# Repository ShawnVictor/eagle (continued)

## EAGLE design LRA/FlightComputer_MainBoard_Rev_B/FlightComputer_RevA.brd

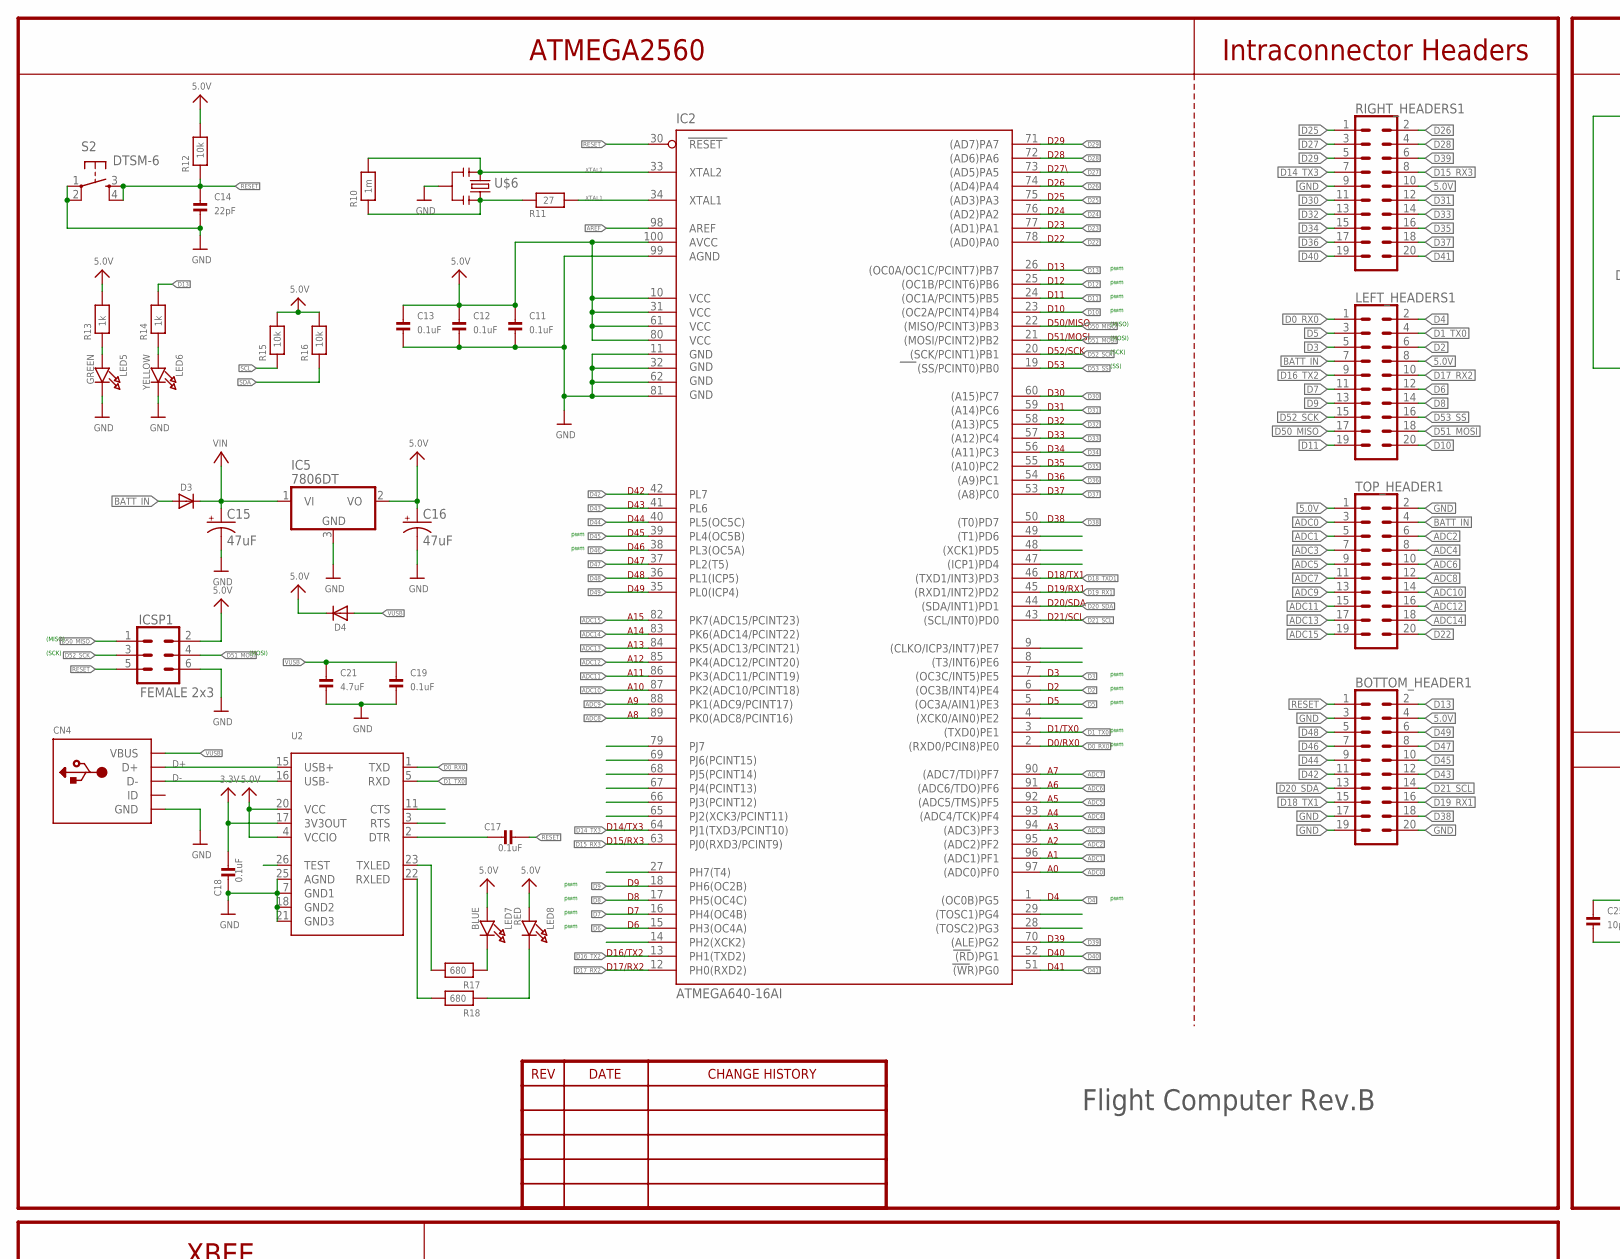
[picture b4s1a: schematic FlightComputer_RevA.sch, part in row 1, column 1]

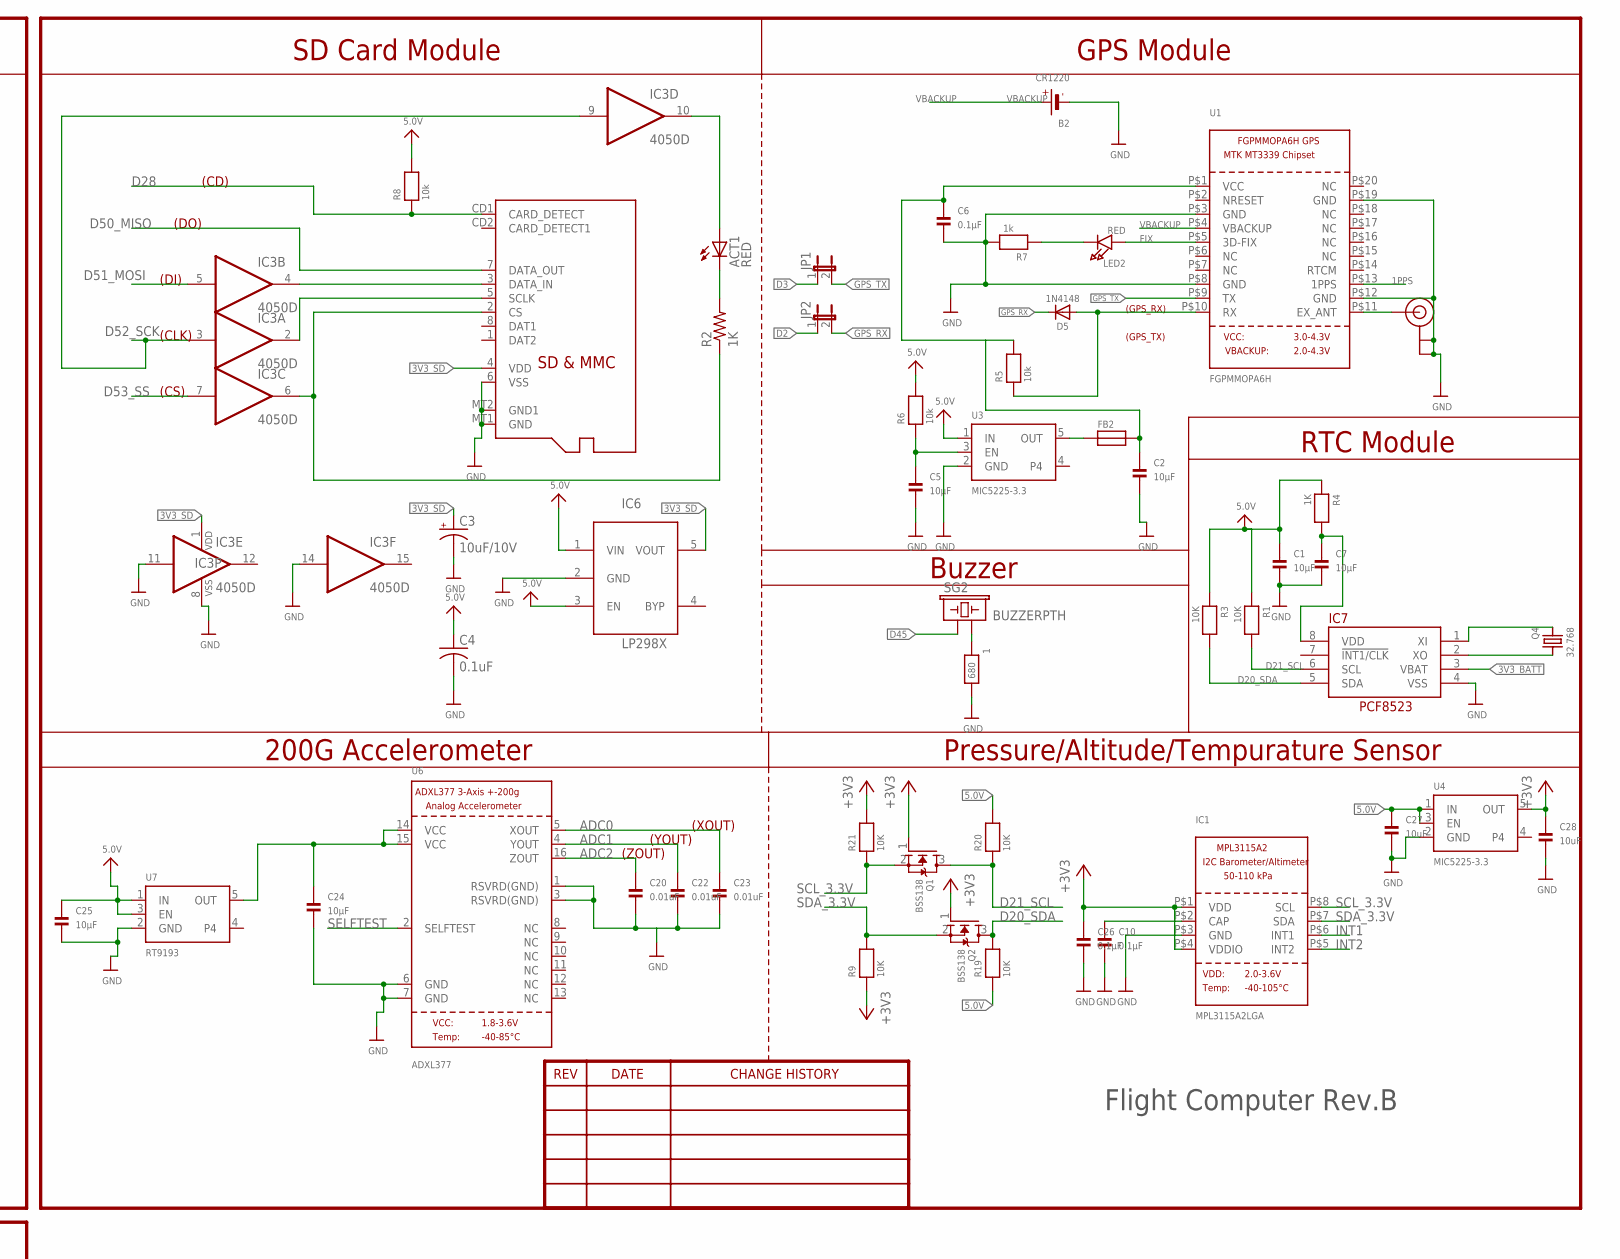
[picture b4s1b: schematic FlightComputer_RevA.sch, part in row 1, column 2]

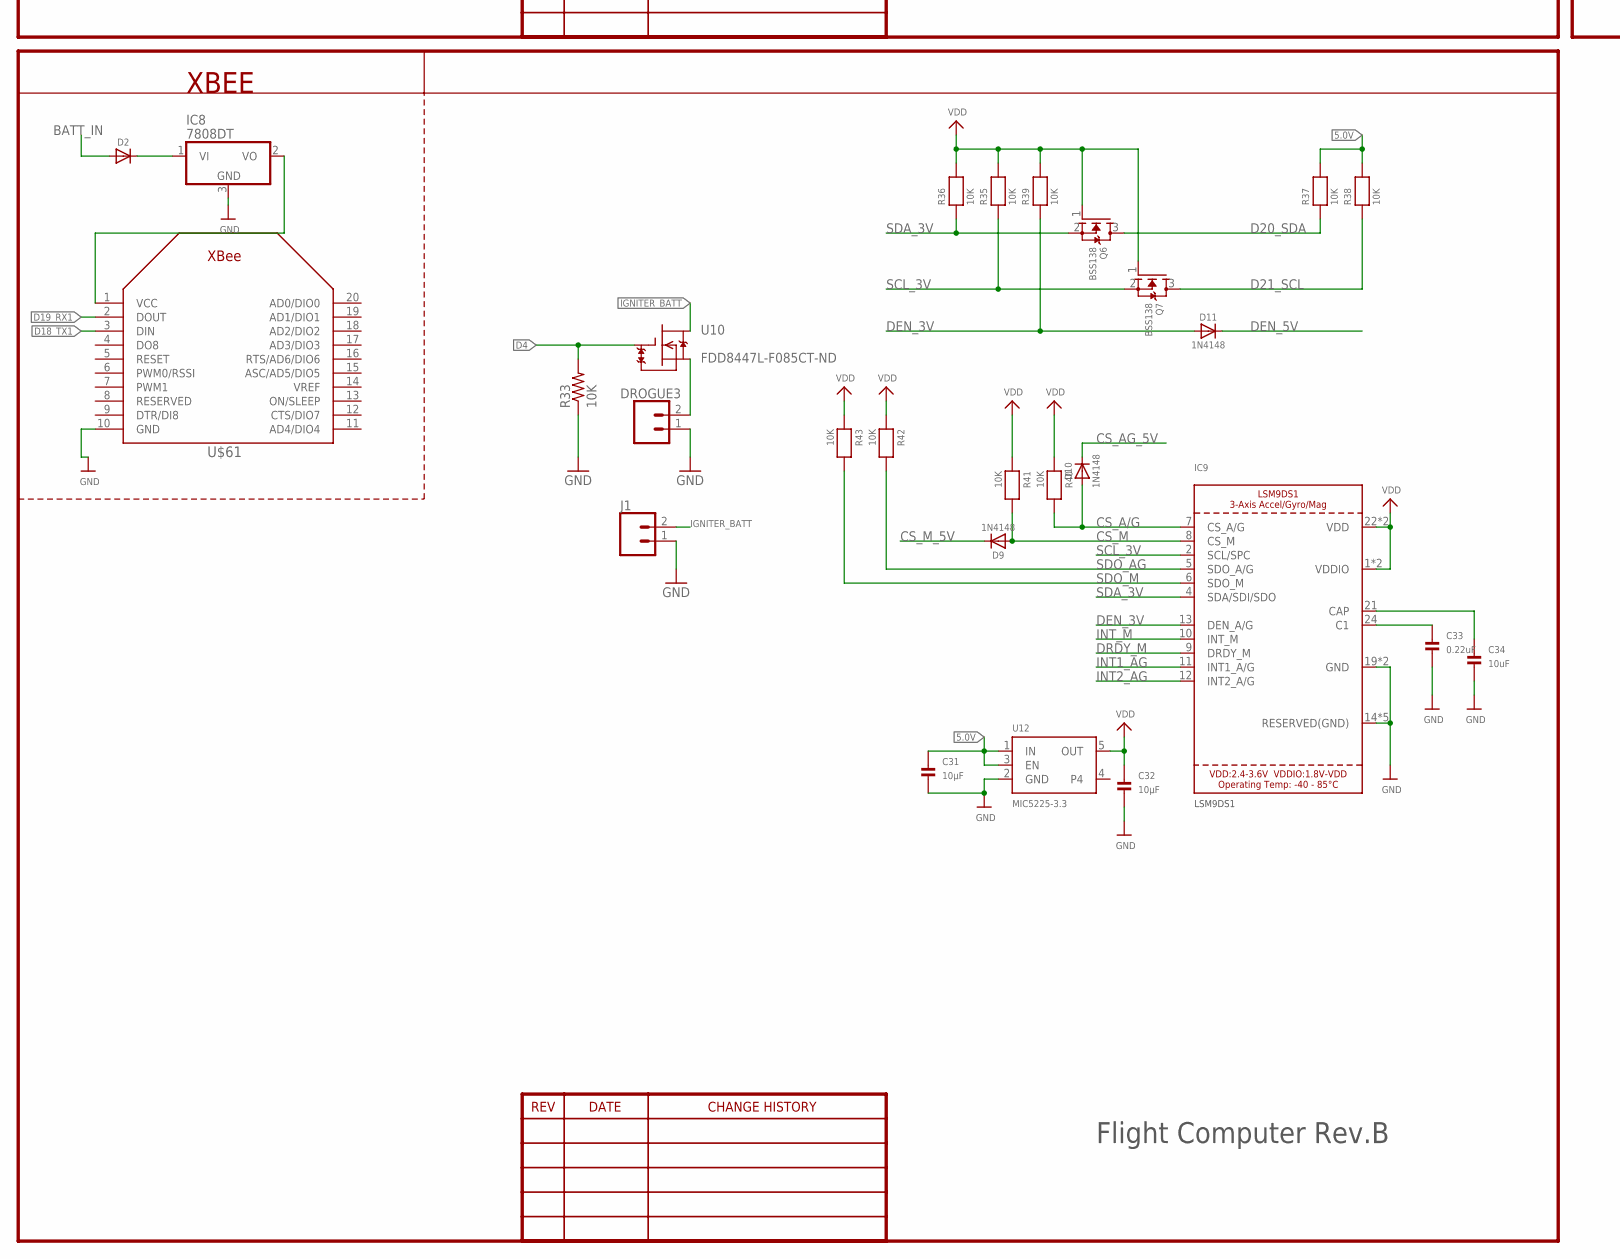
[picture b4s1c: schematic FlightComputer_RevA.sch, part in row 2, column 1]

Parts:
1: 680; 0603
ACT1: RED; CHIP-LED0805
B2: CR1220
BOTTOM_HEADER1: CONN_10X2; 2X10
C1, C2, C5, C7, C24, C25, C31, C32: 10µF; 0603
C3: 10uF/10V; A/3216-18R
C4: 0.1uF; C0805K
C6, C10, C26: 0.1µF; 0603
C11, C12, C13, C17, C18, C19: 0.1uF; 0805
C14: 22pF; 0805
C15, C16: 47uF; PANASONIC_D
C20, C22, C23: 0.01uF; 0603
C21: 4.7uF; 0805
C27, C28, C34: 10uF; 0603
C33: 0.22uF; 0603
CN4: USBMINIB; USB-MINIB
D2, D3, D4: DIODESOD-123; SOD-123
D5, D9, D10, D11: 1N4148; SOD-323
DROGUE3: CONN_023.5MM; SCREWTERMINAL-3.5MM-2
FB2: FERRITE; 0603
IC1: MPL3115A2LGA; LGA8
IC2: ATMEGA640-16AI; TQFP100
IC3: 4050D; SO16
IC5: 7806DT; TO252
IC6: LP298XS; SOT23-5L
IC7: RTC_PCF8523T; SOIC8_150MIL
IC8: 7808DT; TO252
IC9: LSM9DS1; LGA24_3.5X3.1MM
ICSP1: FEMALE 2x3; 2X3
J1: CONN_02; 1X02
JP1, JP2: JUMPER-2SMD-NO-NS; SJ_2S-NO-NS
LED2, LED8: RED; CHIPLED_0805
LED5: GREEN; CHIPLED_0805
LED6: YELLOW; CHIPLED_0805
LED7: BLUE; CHIPLED_0805
LEFT_HEADERS1: CONN_10X2; 2X10
Q1, Q2, Q6, Q7: BSS138; SOT23-WIDE
Q4: 32.768; CRYSTAL_8X3.8
R1, R3, R9, R19, R20, R21, R35, R36, R37, R38, R39, R40, R41, R42, R43: 10K; 0603
R2: 1K; R0805
R4: 1K; 0603
R5, R6, R8: 10k; 0603
R7: 1k; 0603
R10: 1m; 0805
R11: 27; 0805
R12, R15, R16: 10k; 0805
R13, R14: 1k; 0805
R17, R18: 680; 0805
R33: 10K; R0805
RIGHT_HEADERS1: CONN_10X2; 2X10
S2: DTSM-6
SG2: BUZZERPTH; BUZZER-12MM
TOP_HEADER1: CONN_10X2; 2X10
U1: FGPMMOPA6H
U2: FT232RLSSOP28; SSOP28DB
U3, U4, U12: MIC5225-3.3; SOT23-5
U6: ADXL377; LFCSP16_LQ
U7: RT9193; SOT23-5
U10: FDD8447L-F085CT-ND; TO252
U$1: U.FL
U$6: RESONATORSMD; RESONATOR-SMD
U$61: XBEE
X2: MICROSD

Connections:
1PPS: U1.P$13 (1PPS)
3.3V: C18.2, U2.17 (3V3OUT)
3V3_BATT: IC7.3 (VBAT)
3V3_SD: C3.+, IC3.1 (VDD), IC6.5 (VOUT), X2.4 (VDD)
5.0V: BOTTOM_HEADER1.4, C1.1, C4.1, C11.1, C12.1, C13.1, C16.+, C25.1, C27.1, C31.1, D4.C, IC2.10 (VCC), IC2.31 (VCC1), IC2.61 (VCC2), IC2.80 (VCC3), IC2.100 (AVCC), IC5.2 (VO), IC6.1 (VIN), IC6.3 (EN), ICSP1.2, LED7.A, LED8.A, LEFT_HEADERS1.8, R1.1, R3.1, R4.1, R6.2, R8.2, R12.2, R13.2, R15.2, R16.2, R19.1, R20.2, R37.2, R38.2, RIGHT_HEADERS1.10, TOP_HEADER1.1, U2.4 (VCCIO), U2.20 (VCC), U3.1 (IN), U4.1 (IN), U4.3 (EN), U7.1 (IN), U7.3 (EN), U12.1 (IN), U12.3 (EN)
+3V3: C26.1, C28.1, IC1.P$1 (VDD), IC1.P$4 (VDDIO), Q1.1 (G), Q2.1 (G), R9.1, R21.2, U4.5 (OUT)
ADC0: C23.1, IC2.97 ((ADC0)PF0), TOP_HEADER1.3, U6.5 (XOUT)
ADC1: C22.1, IC2.96 ((ADC1)PF1), TOP_HEADER1.5, U6.4 (YOUT)
ADC2: C20.1, IC2.95 ((ADC2)PF2), TOP_HEADER1.6, U6.16 (ZOUT)
ADC3: IC2.94 ((ADC3)PF3), TOP_HEADER1.7
ADC4: IC2.93 ((ADC4/TCK)PF4), TOP_HEADER1.8
ADC5: IC2.92 ((ADC5/TMS)PF5), TOP_HEADER1.9
ADC6: IC2.91 ((ADC6/TDO)PF6), TOP_HEADER1.10
ADC7: IC2.90 ((ADC7/TDI)PF7), TOP_HEADER1.11
ADC8: IC2.89 (PK0(ADC8/PCINT16)), TOP_HEADER1.12
ADC9: IC2.88 (PK1(ADC9/PCINT17)), TOP_HEADER1.13
ADC10: IC2.87 (PK2(ADC10/PCINT18)), TOP_HEADER1.14
ADC11: IC2.86 (PK3(ADC11/PCINT19)), TOP_HEADER1.15
ADC12: IC2.85 (PK4(ADC12/PCINT20)), TOP_HEADER1.16
ADC13: IC2.84 (PK5(ADC13/PCINT21)), TOP_HEADER1.17
ADC14: IC2.83 (PK6(ADC14/PCINT22)), TOP_HEADER1.18
ADC15: IC2.82 (PK7(ADC15/PCINT23)), TOP_HEADER1.19
AREF: IC2.98 (AREF)
BATT_IN: D2.A, D3.A, LEFT_HEADERS1.7, TOP_HEADER1.4
C1: C33.1, IC9.24 (C1)
CAP1: C10.1, IC1.P$2 (CAP)
CAP3: C34.1, IC9.21 (CAP)
CS_A/G: D10.A, IC9.7 (CS_A/G), R40.2
CS_AG_5V: D10.C
CS_M: D9.A, IC9.8 (CS_M), R41.2
CS_M_5V: D9.C
D0_RX0: IC2.2 ((RXD0/PCIN8)PE0), LEFT_HEADERS1.1, U2.1 (TXD)
D1_TX0: IC2.3 ((TXD0)PE1), LEFT_HEADERS1.4, U2.5 (RXD)
D2: IC2.6 ((OC3B/INT4)PE4), JP2.1, LEFT_HEADERS1.6
D3: IC2.7 ((OC3C/INT5)PE5), JP1.1, LEFT_HEADERS1.5
D4: IC2.1 ((OC0B)PG5), LEFT_HEADERS1.2, R33.2, U10.G
D5: IC2.5 ((OC3A/AIN1)PE3), LEFT_HEADERS1.3
D6: IC2.15 (PH3(OC4A)), LEFT_HEADERS1.12
D7: IC2.16 (PH4(OC4B)), LEFT_HEADERS1.11
D8: IC2.17 (PH5(OC4C)), LEFT_HEADERS1.14
D9: IC2.18 (PH6(OC2B)), LEFT_HEADERS1.13
D10: IC2.23 ((OC2A/PCINT4)PB4), LEFT_HEADERS1.20
D11: IC2.24 ((OC1A/PCINT5)PB5), LEFT_HEADERS1.19
D12: IC2.25 ((OC1B/PCINT6)PB6)
D13: BOTTOM_HEADER1.2, IC2.26 ((OC0A/OC1C/PCINT7)PB7), R14.2
D14_TX3: IC2.64 (PJ1(TXD3/PCINT10)), RIGHT_HEADERS1.7
D15_RX3: IC2.63 (PJ0(RXD3/PCINT9)), RIGHT_HEADERS1.8
D16_TX2: IC2.13 (PH1(TXD2)), LEFT_HEADERS1.9
D17_RX2: IC2.12 (PH0(RXD2)), LEFT_HEADERS1.10
D18_TX1: BOTTOM_HEADER1.15, U$61.3 (DIN)
D18_TXD1: IC2.46 ((TXD1/INT3)PD3)
D19_RX1: BOTTOM_HEADER1.16, IC2.45 ((RXD1/INT2)PD2), U$61.2 (DOUT)
D20_SDA: BOTTOM_HEADER1.13, IC2.44 ((SDA/INT1)PD1), IC7.5 (SDA), Q2.3 (D), Q6.3 (D), R3.2, R19.2, R37.1
D21_SCL: BOTTOM_HEADER1.14, IC2.43 ((SCL/INT0)PD0), IC7.6 (SCL), Q1.3 (D), Q7.3 (D), R1.2, R20.1, R38.1
D22: IC2.78 ((AD0)PA0), TOP_HEADER1.20
D23: IC2.77 ((AD1)PA1)
D24: IC2.76 ((AD2)PA2)
D25: IC2.75 ((AD3)PA3), RIGHT_HEADERS1.1
D26: IC2.74 ((AD4)PA4), RIGHT_HEADERS1.2
D27: IC2.73 ((AD5)PA5), RIGHT_HEADERS1.3
D28: IC2.72 ((AD6)PA6), R8.1, RIGHT_HEADERS1.4, X2.CD1 (CARD_DETECT)
D29: IC2.71 ((AD7)PA7), RIGHT_HEADERS1.5
D30: IC2.60 ((A15)PC7), RIGHT_HEADERS1.11
D31: IC2.59 ((A14)PC6), RIGHT_HEADERS1.12
D32: IC2.58 ((A13)PC5), RIGHT_HEADERS1.13
D33: IC2.57 ((A12)PC4), RIGHT_HEADERS1.14
D34: IC2.56 ((A11)PC3), RIGHT_HEADERS1.15
D35: IC2.55 ((A10)PC2), RIGHT_HEADERS1.16
D36: IC2.54 ((A9)PC1), RIGHT_HEADERS1.17
D37: IC2.53 ((A8)PC0), RIGHT_HEADERS1.18
D38: BOTTOM_HEADER1.18, IC2.50 ((T0)PD7)
D39: IC2.70 ((ALE)PG2), RIGHT_HEADERS1.6
D40: IC2.52 ((RD)PG1), RIGHT_HEADERS1.19
D41: IC2.51 ((WR)PG0), RIGHT_HEADERS1.20
D42: BOTTOM_HEADER1.11, IC2.42 (PL7)
D43: BOTTOM_HEADER1.12, IC2.41 (PL6)
D44: BOTTOM_HEADER1.9, IC2.40 (PL5(OC5C))
D45: BOTTOM_HEADER1.10, IC2.39 (PL4(OC5B)), SG2.+ (1)
D46: BOTTOM_HEADER1.7, IC2.38 (PL3(OC5A))
D47: BOTTOM_HEADER1.8, IC2.37 (PL2(T5))
D48: BOTTOM_HEADER1.5, IC2.36 (PL1(ICP5))
D49: BOTTOM_HEADER1.6, IC2.35 (PL0(ICP4))
D50_MISO: IC2.22 ((MISO/PCINT3)PB3), ICSP1.1, LEFT_HEADERS1.17, X2.7 (DATA_OUT)
D51_MOSI: IC2.21 ((MOSI/PCINT2)PB2), IC3.5 (I), ICSP1.4, LEFT_HEADERS1.18
D52_SCK: IC2.20 ((SCK/PCINT1)PB1), IC3.3 (I), IC3.9 (I), ICSP1.3, LEFT_HEADERS1.15
D53_SS: IC2.19 ((SS/PCINT0)PB0), IC3.7 (I), LEFT_HEADERS1.16
D+: CN4.D+, U2.15 (USB+)
D-: CN4.D-, U2.16 (USB-)
DEN_3V: D11.A, IC9.13 (DEN_A/G), R39.1
DEN_5V: D11.C
DRDY_M: IC9.9 (DRDY_M)
FIX: LED2.A, U1.P$5 (3D-FIX)
GND: 1.2, B2.-, BOTTOM_HEADER1.3, BOTTOM_HEADER1.17, BOTTOM_HEADER1.19, BOTTOM_HEADER1.20, C1.2, C2.2, C3.-, C4.2, C5.2, C6.2, C7.2, C10.2, C11.2, C12.2, C13.2, C14.2, C15.-, C16.-, C18.1, C19.1, C20.2, C21.1, C22.2, C23.2, C24.2, C25.2, C26.2, C27.2, C28.2, C31.2, C32.2, C33.2, C34.2, CN4.GND, DROGUE3.1, IC1.P$3 (GND), IC2.11 (GND), IC2.32 (GND1), IC2.62 (GND2), IC2.81 (GND3), IC2.99 (AGND), IC3.8 (VSS), IC3.11 (I), IC3.14 (I), IC5.3 (GND), IC6.2 (GND), IC7.4 (VSS), IC8.3 (GND), IC9.14 (RESERVED(GND)), IC9.15 (RESERVED(GND)), IC9.16 (RESERVED(GND)), IC9.17 (RESERVED(GND)), IC9.18 (RESERVED(GND)), IC9.19 (GND), IC9.20 (GND), ICSP1.6, J1.1, LED5.C, LED6.C, R7.2, R33.1, RIGHT_HEADERS1.9, S2.1, S2.2, TOP_HEADER1.2, U1.P$3 (GND), U1.P$8 (GND), U1.P$12 (GND), U1.P$19 (GND), U2.7 (GND1), U2.18 (GND2), U2.21 (GND3), U2.25 (AGND), U3.2 (GND), U4.2 (GND), U6.1 (RSVRD(GND)), U6.3 (RSVRD(GND)), U6.6 (GND), U6.7 (GND), U7.2 (GND), U12.2 (GND), U$1.P$1 (GND), U$1.P$2 (GND), U$6.2, U$61.10 (GND), X2.6 (VSS), X2.MT1 (GND), X2.MT2 (GND1)
GPS_RX: D5.C, JP2.2
GPS_TX: JP1.2, U1.P$9 (TX)
IGNITER_BATT: J1.2, U10.D
INT1: IC1.P$6 (INT1)
INT1_AG: IC9.11 (INT1_A/G)
INT2: IC1.P$5 (INT2)
INT2_AG: IC9.12 (INT2_A/G)
INT_M: IC9.10 (INT_M)
unnamed: IC7.1 (XI), Q4.P$1 (1)
unnamed: IC7.2 (XO), Q4.P$4 (2)
unnamed: ACT1.A, IC3.10 (O)
unnamed: IC3.2 (O), X2.5 (SCLK)
unnamed: IC3.6 (O), R2.1, X2.2 (CS)
unnamed: ACT1.C, R2.2
unnamed: IC3.4 (O), X2.3 (DATA_IN)
unnamed: C7.1, IC7.8 (VDD), R4.2
unnamed: U1.P$11 (EX_ANT), U$1.P$3 (SIGNAL)
unnamed: D5.A, R5.1, U1.P$10 (RX)
unnamed: C2.1, C6.1, FB2.2, R5.2, U1.P$1 (VCC)
unnamed: R10.1, R11.2, U$6.3
unnamed: C5.1, R6.1, U3.3 (EN)
unnamed: LED2.C, R7.1
unnamed: D2.C, IC8.1 (VI)
unnamed: 1.1, SG2.- (2)
unnamed: C24.1, IC2.14 (PH2(XCK2)), U6.14 (VCC), U6.15 (VCC), U7.5 (OUT)
unnamed: LED5.A, R13.1
unnamed: LED6.A, R14.1
unnamed: LED8.C, R18.1
unnamed: LED7.C, R17.1
unnamed: C17.1, U2.2 (DTR)
unnamed: R18.2, U2.22 (RXLED)
unnamed: R17.2, U2.23 (TXLED)
OUT: FB2.1, U3.5 (OUT)
RESET: BOTTOM_HEADER1.1, C14.1, C17.2, IC2.30 (RESET), ICSP1.5, R12.1, S2.3, S2.4
SCL: R15.1
SCL_3.3V: IC1.P$8 (SCL), Q1.2 (S), R21.1
SCL_3V: IC9.2 (SCL/SPC), Q7.2 (S), R35.1
SDA: R16.1
SDA_3.3V: IC1.P$7 (SDA), Q2.2 (S), R9.2
SDA_3V: IC9.4 (SDA/SDI/SDO), Q6.2 (S), R36.1
SDO_AG: IC9.5 (SDO_A/G), R42.2
SDO_M: IC9.6 (SDO_M), R43.2
SELFTEST: U6.2 (SELFTEST)
SOURCE2: DROGUE3.2, U10.S
VBACKUP: B2.+$1 (+), B2.+$2 (+), U1.P$4 (VBACKUP)
VCC: IC8.2 (VO), U$61.1 (VCC)
VDD: C32.1, IC9.1 (VDDIO), IC9.3 (VDDIO), IC9.22 (VDD), IC9.23 (VDD), Q6.1 (G), Q7.1 (G), R35.2, R36.2, R39.2, R40.1, R41.1, R42.1, R43.1, U12.5 (OUT)
VIN: C15.+, D3.C, IC5.1 (VI)
VUSB: C19.2, C21.2, CN4.VBUS, D4.A
XTAL1: IC2.34 (XTAL1), R11.1
XTAL2: IC2.33 (XTAL2), R10.2, U$6.1

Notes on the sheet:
Intraconnector Headers
pwm
(SS)
(SCK)
(MOSI)
(MISO)
D42
D43
D44
D45
D46
D47
D48
D49
A15
A14
A13
A12
A11
A10
D14/TX3
D15/RX3
D16/TX2
D17/RX2
D29
D28
D27\
D26
D25
D24
D23
D22
D13
D12
D11
D10
D50/MISO
D51/MOSI
D52/SCK
D53

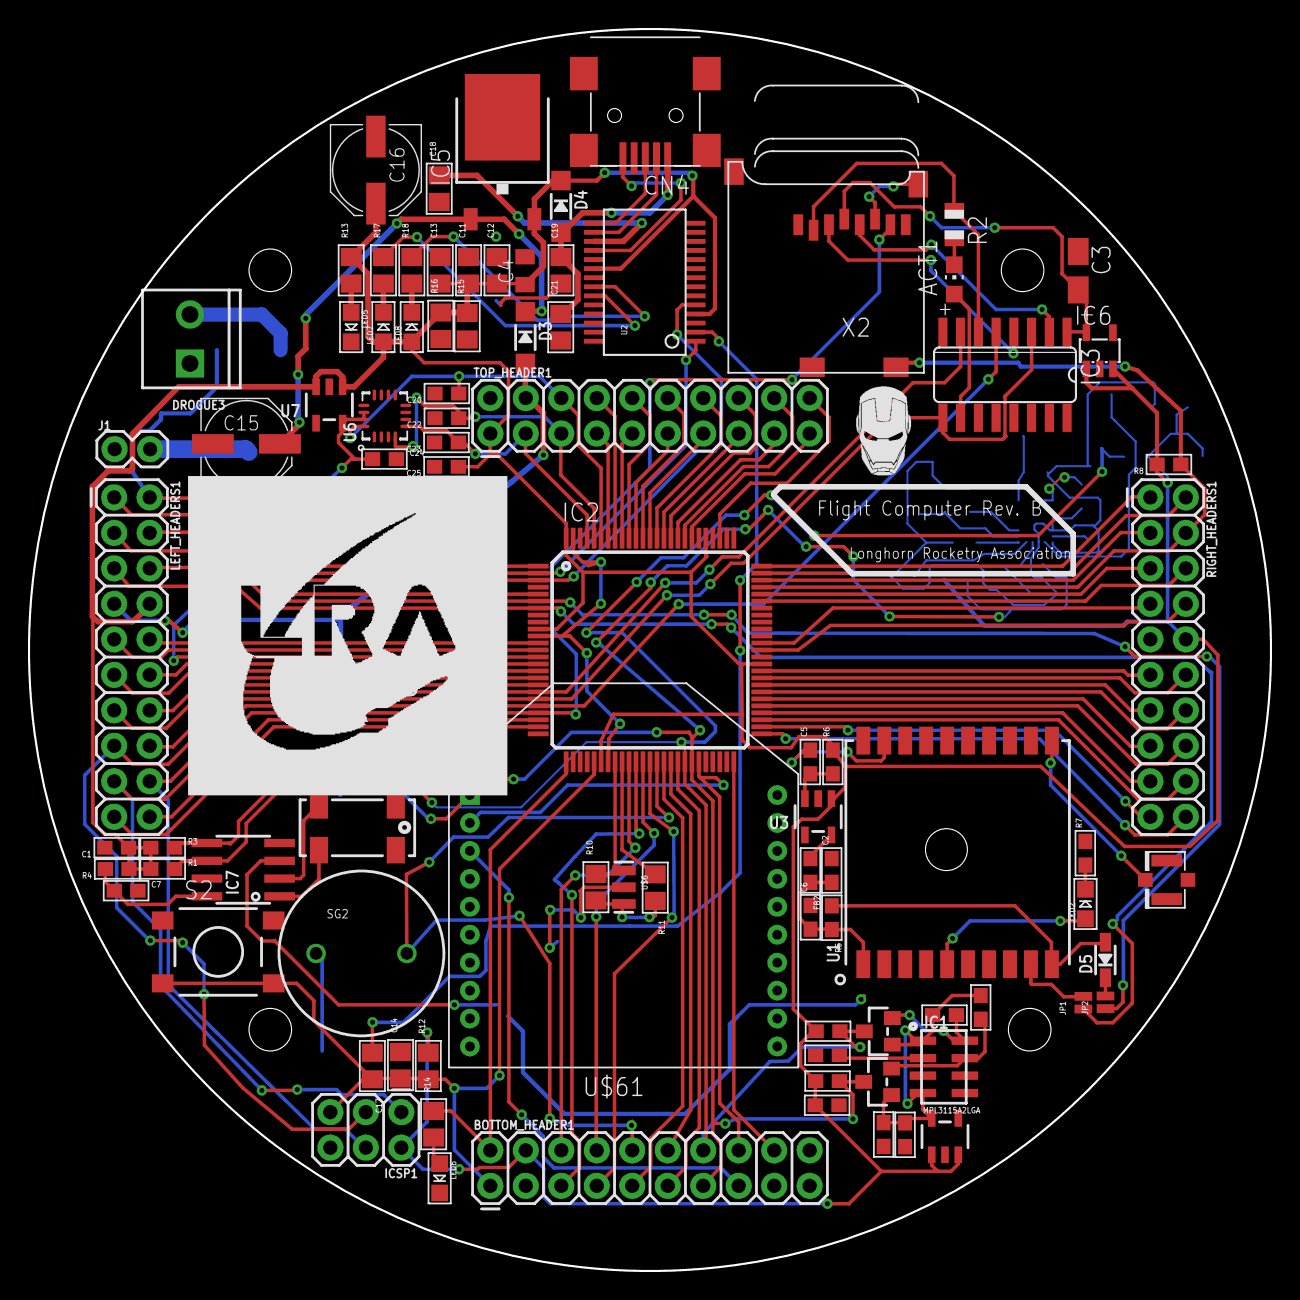
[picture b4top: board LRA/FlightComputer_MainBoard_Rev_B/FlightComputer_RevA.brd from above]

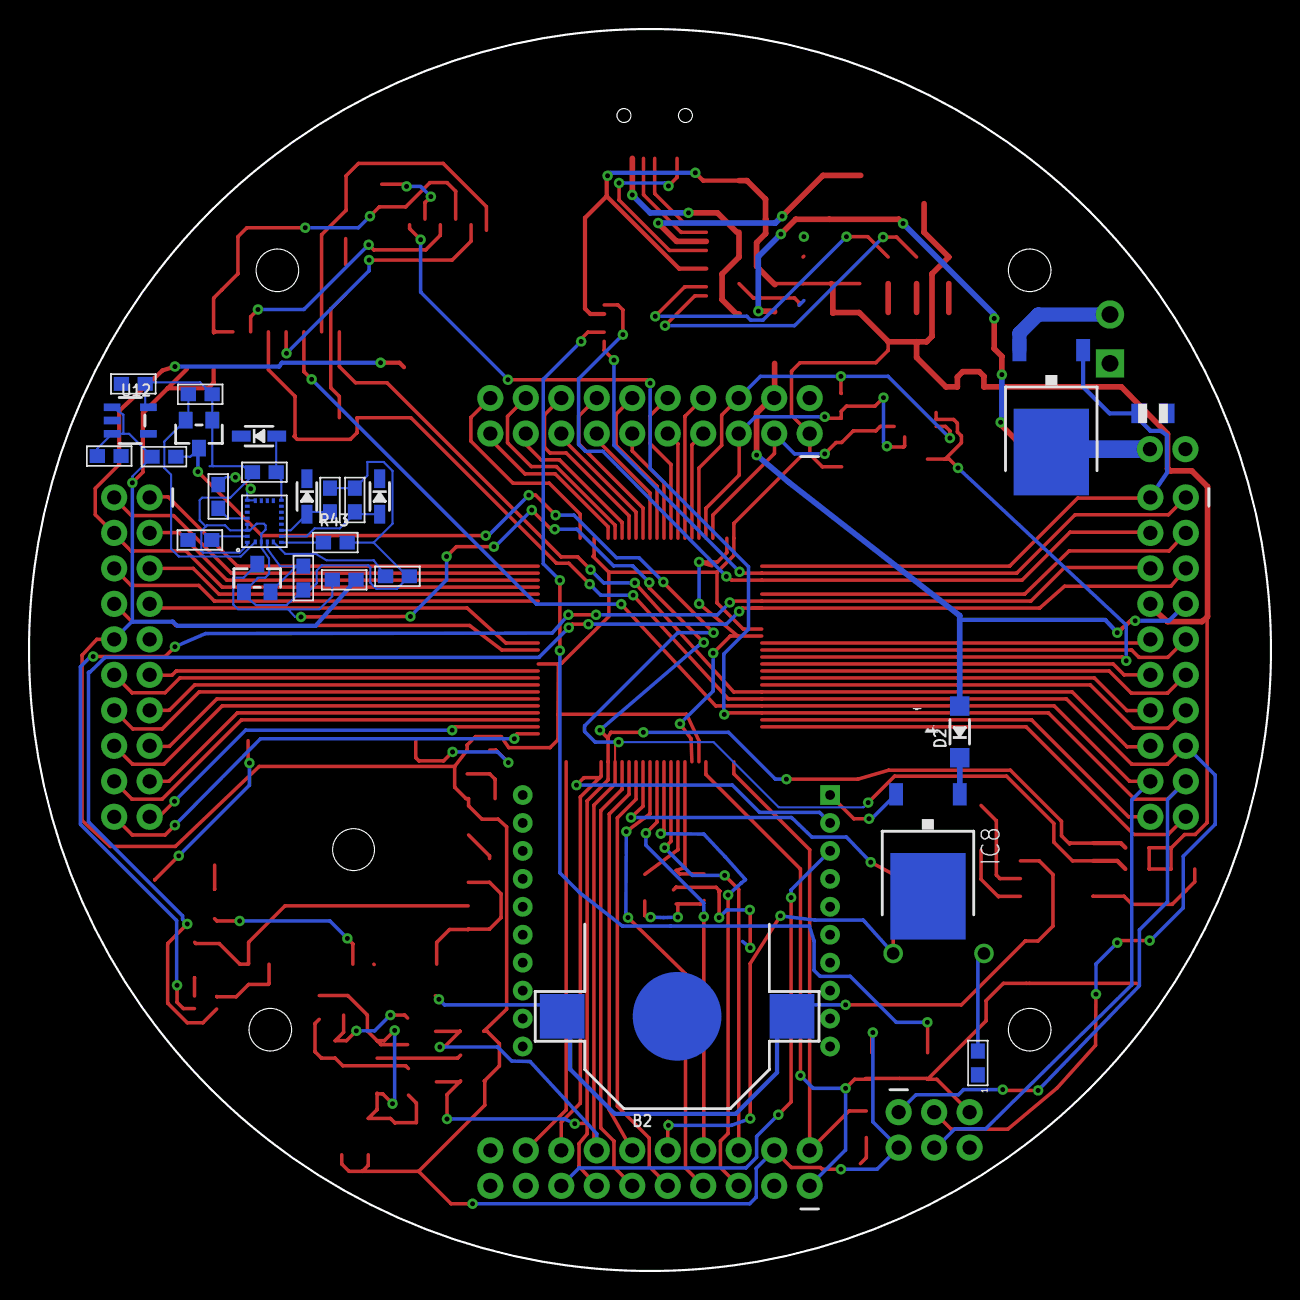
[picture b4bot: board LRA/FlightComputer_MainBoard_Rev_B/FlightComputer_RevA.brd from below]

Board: 2 copper layers, 88.9 x 88.9 mm, 114 parts (26 on the bottom side), 125 nets.

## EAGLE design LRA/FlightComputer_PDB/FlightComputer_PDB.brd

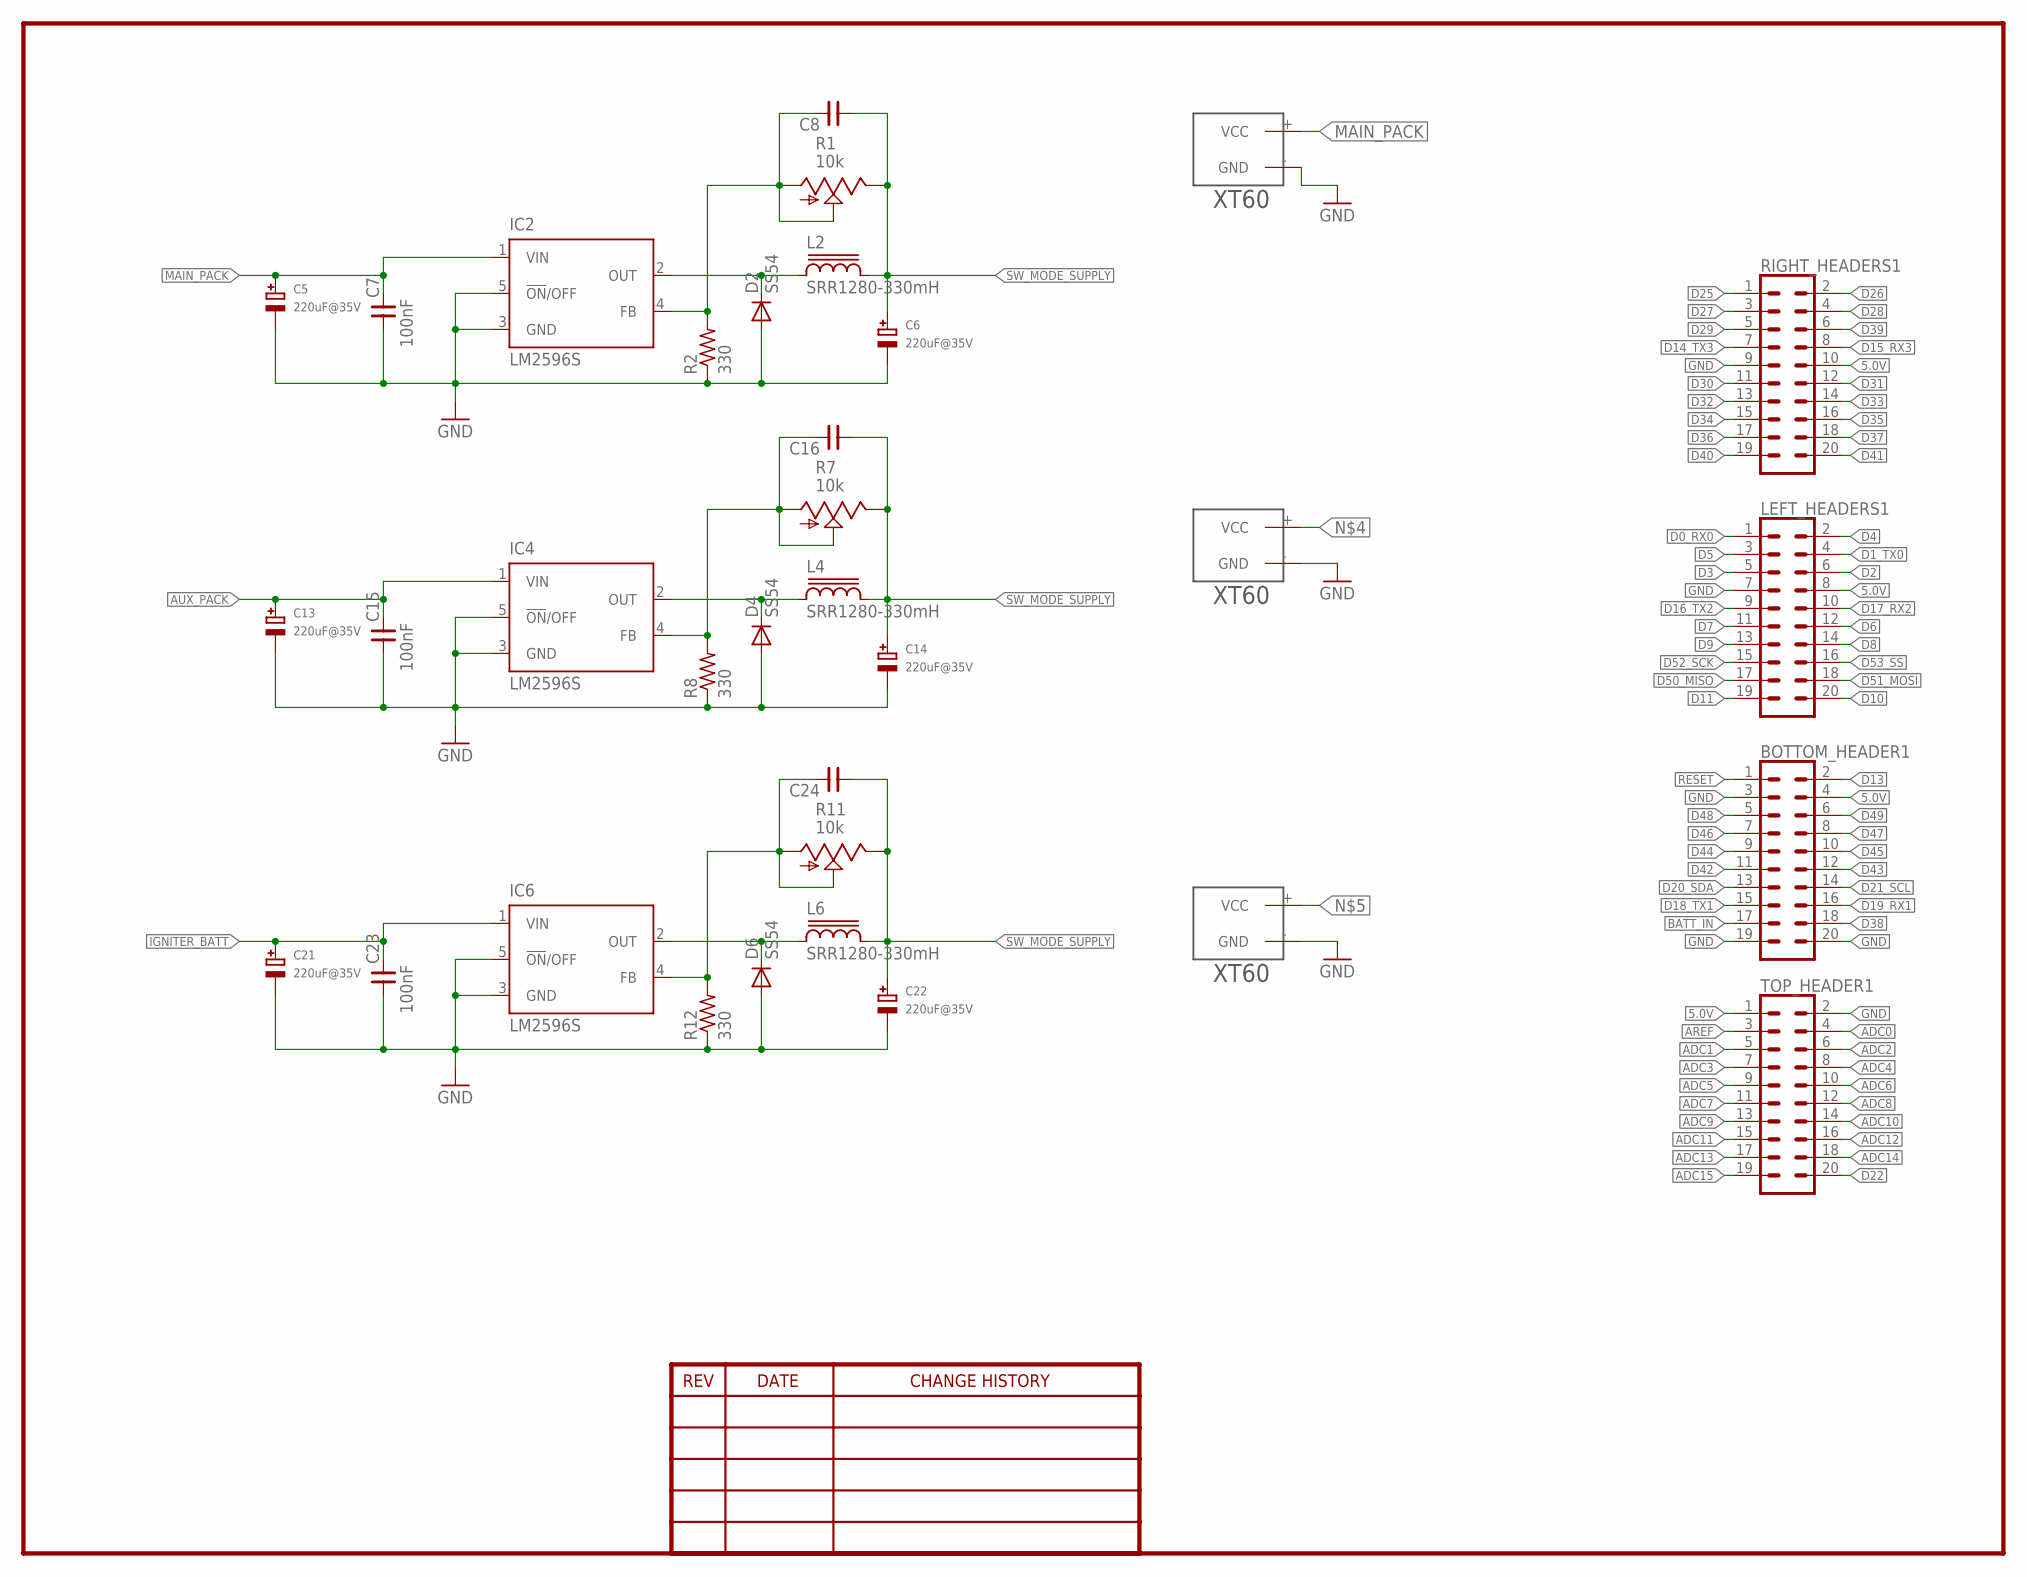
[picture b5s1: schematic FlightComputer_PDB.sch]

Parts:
BOTTOM_HEADER1: CONN_10X2; 2X10
C5, C6, C13, C14, C21, C22: 220uF@35V; PANASONIC_D
C7, C15, C23: 100nF; 0603
C8, C16, C24: CNP-0603; 0603
D2, D4, D6: SS54; DO214AB
IC2, IC4, IC6: LM2596S; TO263-5
L2, L4, L6: SRR1280-330mH; SRR1280
LEFT_HEADERS1: CONN_10X2; 2X10
R1, R7, R11: 10k; S64W
R2, R8, R12: 330; R0603
RIGHT_HEADERS1: CONN_10X2; 2X10
TOP_HEADER1: CONN_10X2; 2X10
U$1, U$2, U$3: XT60

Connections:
5.0V: BOTTOM_HEADER1.4, LEFT_HEADERS1.8, RIGHT_HEADERS1.10, TOP_HEADER1.1
ADC0: TOP_HEADER1.4
ADC1: TOP_HEADER1.5
ADC2: TOP_HEADER1.6
ADC3: TOP_HEADER1.7
ADC4: TOP_HEADER1.8
ADC5: TOP_HEADER1.9
ADC6: TOP_HEADER1.10
ADC7: TOP_HEADER1.11
ADC8: TOP_HEADER1.12
ADC9: TOP_HEADER1.13
ADC10: TOP_HEADER1.14
ADC11: TOP_HEADER1.15
ADC12: TOP_HEADER1.16
ADC13: TOP_HEADER1.17
ADC14: TOP_HEADER1.18
ADC15: TOP_HEADER1.19
AREF: TOP_HEADER1.3
AUX_PACK: C13.+, C15.2, IC4.1 (VIN)
BATT_IN: BOTTOM_HEADER1.17
D0_RX0: LEFT_HEADERS1.1
D1_TX0: LEFT_HEADERS1.4
D2: LEFT_HEADERS1.6
D3: LEFT_HEADERS1.5
D4: LEFT_HEADERS1.2
D5: LEFT_HEADERS1.3
D6: LEFT_HEADERS1.12
D7: LEFT_HEADERS1.11
D8: LEFT_HEADERS1.14
D9: LEFT_HEADERS1.13
D10: LEFT_HEADERS1.20
D11: LEFT_HEADERS1.19
D13: BOTTOM_HEADER1.2
D14_TX3: RIGHT_HEADERS1.7
D15_RX3: RIGHT_HEADERS1.8
D16_TX2: LEFT_HEADERS1.9
D17_RX2: LEFT_HEADERS1.10
D18_TX1: BOTTOM_HEADER1.15
D19_RX1: BOTTOM_HEADER1.16
D20_SDA: BOTTOM_HEADER1.13
D21_SCL: BOTTOM_HEADER1.14
D22: TOP_HEADER1.20
D25: RIGHT_HEADERS1.1
D26: RIGHT_HEADERS1.2
D27: RIGHT_HEADERS1.3
D28: RIGHT_HEADERS1.4
D29: RIGHT_HEADERS1.5
D30: RIGHT_HEADERS1.11
D31: RIGHT_HEADERS1.12
D32: RIGHT_HEADERS1.13
D33: RIGHT_HEADERS1.14
D34: RIGHT_HEADERS1.15
D35: RIGHT_HEADERS1.16
D36: RIGHT_HEADERS1.17
D37: RIGHT_HEADERS1.18
D38: BOTTOM_HEADER1.18
D39: RIGHT_HEADERS1.6
D40: RIGHT_HEADERS1.19
D41: RIGHT_HEADERS1.20
D42: BOTTOM_HEADER1.11
D43: BOTTOM_HEADER1.12
D44: BOTTOM_HEADER1.9
D45: BOTTOM_HEADER1.10
D46: BOTTOM_HEADER1.7
D47: BOTTOM_HEADER1.8
D48: BOTTOM_HEADER1.5
D49: BOTTOM_HEADER1.6
D50_MISO: LEFT_HEADERS1.17
D51_MOSI: LEFT_HEADERS1.18
D52_SCK: LEFT_HEADERS1.15
D53_SS: LEFT_HEADERS1.16
GND: BOTTOM_HEADER1.3, BOTTOM_HEADER1.19, BOTTOM_HEADER1.20, C5.-, C6.-, C7.1, C13.-, C14.-, C15.1, C21.-, C22.-, C23.1, D2.A, D4.A, D6.A, IC2.3 (GND), IC2.5 (!ON!/OFF), IC4.3 (GND), IC4.5 (!ON!/OFF), IC6.3 (GND), IC6.5 (!ON!/OFF), LEFT_HEADERS1.7, R2.1, R8.1, R12.1, RIGHT_HEADERS1.9, TOP_HEADER1.2, U$1.- (GND), U$2.- (GND), U$3.- (GND)
IGNITER_BATT: C21.+, C23.2, IC6.1 (VIN)
MAIN_PACK: C5.+, C7.2, IC2.1 (VIN), U$1.+ (VCC)
unnamed: D2.C, IC2.2 (OUT), L2.1
unnamed: C8.2, IC2.4 (FB), R1.A, R1.S, R2.2
unnamed: D4.C, IC4.2 (OUT), L4.1
unnamed: C16.2, IC4.4 (FB), R7.A, R7.S, R8.2
unnamed: D6.C, IC6.2 (OUT), L6.1
unnamed: C24.2, IC6.4 (FB), R11.A, R11.S, R12.2
RESET: BOTTOM_HEADER1.1
SW_MODE_SUPPLY: C6.+, C8.1, C14.+, C16.1, C22.+, C24.1, L2.2, L4.2, L6.2, R1.E, R7.E, R11.E

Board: 2 copper layers, 34 parts (0 on the bottom side), 12 nets, no tracks yet.
